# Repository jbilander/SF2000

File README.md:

# SF2000
Spitfire 2000, A low-end 42 MHz Amiga Accelerator based on the Motorola 68SEC000 CPU
 
***
 
This is WORK IN PROGRESS, a DIY hobby project. If you are going to make and sell boards you are also the one doing the customer support.
 
**Revision 3A is brand new and has not been tested yet.**
 
IMPORTANT **Please do not build Revision 2B.** We have found problems with the bus isolation on that revision which cause SRAM corruption. The Rev. 2B and Rev. 1B bills of material further down are kept for reference only.
 
***
 
The firmware for this board is in a separate repository available here: <br />
https://github.com/jbilander/SF2000-FW
<br />
 
***
 
Revision 3A
<br />

<br />
Full schematic: <a href="images/SF2000_rev3a_schematic.pdf">SF2000_rev3a_schematic.pdf</a>
 
***
 
Revision 1B
<br />

***

***
 
BOM Rev. 3A
---------
Rev. 3A replaces the four asynchronous SRAMs with a single SDRAM, swaps the Efinix Trion for an Intel/Altera MAX 10,
drops the on-board IDE interface, and adds an ESP32-C5 module and an RP2354A. Values and packages below are taken
straight from the KiCad netlist.
 
Designator  | Name/Value   | Package | Notes
-|-|-|-|
U1 | Voltage Regulator 3.3V, <br /> LM1117-3.3 or <br /> AMS1117-3.3 | SOT-223 | 3.3V 1A Low Drop-Out (LDO) Linear Voltage Regulator, main `3V3` rail <br />[LM111733QDCYRQ1](https://www.mouser.com/en/ProductDetail/595-LM111733QDCYRQ1) is the automotive-qualified LM1117-3.3 in SOT-223-4; any ordinary LM1117-3.3 in SOT-223 does the same job, and AMS1117-3.3 from AliExpress is a cheap alternative
U2 | Voltage Regulator 4.3V, ABLIC S-1132B43-M5T1U or TPS73643DBVR | SOT-23-5 | 4.3V LDO, the `4V3` supply rail for the CBT FET bus switches U4,U5,U6 <br />[S-1132B43-M5T1U](https://www.mouser.com/en/ProductDetail/628-S-1132B43-M5T1G)
U3 | Voltage Regulator 3.3V, TLV75533PDBVR | SOT-23-5 | 3.3V 500mA LDO, separate `3V3_C5` rail for the ESP32-C5 module so its Wi-Fi bursts stay off the FPGA rail <br />[TLV75533PDBVR](https://www.mouser.com/en/ProductDetail/595-TLV75533PDBVR)
U4,U5 | Digital Bus Switch 24-Bit FET, SN74CBT16211CDGGR or SN74CBT16811CDGGR | TSSOP-56 | FET level-shifter, Amiga +5V bus <-> 3V3 <br />[SN74CBT16211CDGGR](https://www.mouser.com/en/ProductDetail/595-SN74CBT16211CDGG) (Mouser's own part number drops the trailing R, but it is the cut-tape CDGGR)
U6 | Digital Bus Switch 10-Bit FET, SN74CBT3244PW | TSSOP-20 | FET level-shifter for the remaining control lines <br />[SN74CBT3244PW](https://www.mouser.com/en/ProductDetail/595-SN74CBT3244PW)
U7 | Bus Transceiver 16-Bit, SN74LVC16245ADGGR | TSSOP-48 | Buffers the D0-D15 data bus, direction and output-enable driven by the FPGA (`DATA_DIR`, `OE_D_HIGH`, `OE_D_LOW`) <br />[SN74LVC16245ADGGR](https://www.mouser.com/en/ProductDetail/595-SNLVC16245ADGGR)
U8 | Intel/Altera MAX 10 FPGA, 10M04SCU324C8G | BGA-324, 15x15mm, 0.8mm pitch | 4000 LE, internal configuration flash and UFM. It has to be the `S` **single-supply** variant - there is no 1.2V core rail on this board. The symbol and footprint in KiCad are drawn as a 10M02 so the design can be downsized to a 10M02SCU324 later if it fits; the firmware is developed for the 10M04 <br />[10M04SCU324C8G](https://www.mouser.com/en/ProductDetail/989-10M04SCU324C8G) / [10M02SCU324C8G](https://www.mouser.com/en/ProductDetail/989-10M02SCU324C8G)
U9 | W25Q16JVSNIQ 16 Mbit SPI NOR Flash memory | SOIC-8_3.9x4.9mm_P1.27mm (150-mil Narrow JEDEC SOIC) | [W25Q16JVSNIQ](https://www.digikey.com/en/products/detail/winbond-electronics/w25q16jvsniq/6193768) or [AT25SF161B-SSHD-T](https://www.mouser.com/en/ProductDetail/724-AT25SF161BSSHDT)
U10 | Motorola CPU MC68SEC000AA20 20MHz | QFP-64_14x14mm_Pitch0.8mm | [MC68SEC000AA20](https://shop.tvsat.com.pl/en_GB/searchquery/68sec000/1/phot/5?url=68sec000)
U11 | SDRAM 8Mx16 (128 Mbit), <br /> IM1216SDBABG-6I or <br /> AS4C8M16SA-6BINTR | TFBGA-54, 8x8mm, 0.8mm pitch | Replaces the four SRAMs of Rev. 2B. 128 Mbit is 16 MB, which is the whole address space the MC68SEC000 can reach, so there is nothing to gain from a bigger part. The footprint is routed for all 13 address lines, so a 256 Mbit 16Mx16 part (AS4C16M16SA-6BIN) drops straight in as well should a large shadow RAM ever want one - unlikely, but the option costs nothing. On the 128 Mbit parts ball F9 (`A12`) is a no-connect, so the controller's row-address width has to match whichever density is fitted. On the Alliance part the `-6BINTR` suffix is cut tape and `-6BIN` is the tray version of the same device, which costs noticeably more <br />[IM1216SDBABG-6I](https://www.mouser.com/en/ProductDetail/822-IM1216SDBABG-6I) / [AS4C8M16SA-6BINTR](https://www.mouser.com/en/ProductDetail/913-4C8M16SA-6BINTR)
U12 | 74HCT2G14GV,125 Dual Schmitt Trigger Inverter | TSOP-6 / SOT457 / SC-74 | Drives the SD_LED header J9 and the /SD_ACTIVE pin J10 at +5V <br />[74HCT2G14GV,125](https://www.mouser.com/en/ProductDetail/771-HCT2G14GV125)
U13 | ESP32-C5-WROOM-1U-N8R8 | Module, 18 x 25.5mm, U.FL antenna connector | The `-1U` variant uses an external antenna, so no PCB antenna keep-out is needed under or beside the module. If you fit the PCB-antenna `-1` variant instead, the module has to be moved so its antenna end hangs over the board edge <br />[ESP32-C5-WROOM-1U-N8R8](https://www.mouser.com/en/ProductDetail/356-ESP32C5WRM1UN8R8) / [ESP32-C5-WROOM-1-N8R8](https://www.mouser.com/en/ProductDetail/356-ESP32C5WROM1N8R8)
U14 | Level shifter 74LVC8T245PW,118 | TSSOP-24 | Clockport data bus CP_D0-CP_D7. 3V3 on the A side, +5V on the B side, direction and enable from the FPGA <br />[74LVC8T245PW,118](https://www.mouser.com/en/ProductDetail/771-74LVC8T245PW118)
U15 | Level shifter 74LVC8T245PW,118 | TSSOP-24 | Clockport address and control (CP_A2-CP_A5, /CS, /IORD, /IOWR). +5V on the A side, 3V3 on the B side, DIR and /OE tied low so it always drives 3V3 -> +5V <br />[74LVC8T245PW,118](https://www.mouser.com/en/ProductDetail/771-74LVC8T245PW118)
U16 | Raspberry Pi RP2354A | QFN-60, 7x7mm, 0.4mm pitch | MCU with 2 MB stacked flash. SPI slave to the FPGA (`SS_RP2354`, `IRQ_RP2354`) plus a UART link to the ESP32-C5 <br />[RP2354A (SC1511-A4)](https://www.mouser.com/en/ProductDetail/358-SC151113)
U17 | 74LVC1G57GV Configurable Multiple-Function Gate | TSOP-6 / SOT457 / SC-88A | Wired as XNOR with A and B tied together: CLK7M = CCK XNOR CCKQ (replaces the SN74LVC2G86DCUR XOR of Rev. 2B). This is how the 7 MHz is generated on every supported machine - the real 7M is not present on the co-pro slot of the early German A2000, nor on A500 Rev 3 and Rev 5, but CCK and CCKQ always are <br />[74LVC1G57GV,125](https://www.mouser.com/en/ProductDetail/771-LVC1G57GV125)
J1 | Goldfingers on PCB, 86-pin | ENIG | Order PCB with Goldfingers, ENIG and 45 degrees chamfered edge (or chamfer the edge yourself with a file)
J2 | CFGIN-header, Two-Pin Header | 2.54mm (1 x 2) | Put a jumper shunt here to activate autoconfig, or a CONFIGOUT-wire from another device into pin 2. Pin 2 is pulled up to +5V by R21
J3 | JTAG-header | Dual row 2.54mm (2 x 5) Pin Male Header |
J4 | JP-header JP2, JP3 | 2.54mm (2 x 2) Pin Male Header | JP2 = Generate E-CLK (if the internal 68k is removed from the socket), JP3 = MapROM
J5 | SWD pads, SWCLK / GND / SWDIO | 2.54mm (1 x 3) | Serial Wire Debug for U16 (RP2354A)
J6 | ESP32 UART0, TX0 / RX0 | 2.54mm (1 x 2) Pin Male Header | Console and flashing header for U13
J7 | VCC/GND Two-Pin Header | 2.54mm (2 x 1) | VIN +5V <br /> used when programming the FPGA standalone (card not installed in the Amiga). Be careful with orientation, check polarity BEFORE plugging-in a phone charger or similar here
J8 | GCT MEM2055-00-190-01-A Micro SD Card Socket | 9-pin push-pull micro-SD socket | Wired for 4-bit SDIO as well as 1-bit SPI: SD_CS=DAT3, SD_MOSI=CMD, SD_MISO=DAT0, SD_D1=DAT1, SD_D2=DAT2
J9 | SD_LED header, Two-Pin Header | 2.54mm (2 x 1) | Driven by U12 inverter buffer when /SD_CS is being asserted. Connect here to drive an external HDD-LED
J10 | SD_ACTIVE low signal, Right angle Single-Pin Header | 0.64 mm square pin angled | Driven by U12 inverter buffer when /SD_CS is being asserted. Connect from here to a [LED-board](https://github.com/jbilander/A500_IDE_LED_board) (Active low +5V-signal)
J11 | RP2354A UART0, TX0 / RX0 | 2.54mm (1 x 2) Pin Male Header | Console header for U16
J12 | CLOCKPORT-header | 2.00mm 22-Pin (2x11) Pin Male Header | Caution: This header is +5V levels. Be careful with orientation
J13 | JP-header JP1 | 2.54mm (2 x 1) Pin Male Header | 7 MHz / Turbo selector
J14 | USB-C Receptacle USB 2.0, HRO TYPE-C-31-M-12 | 16-pin SMD | Native USB for the ESP32-C5 (U13)
J15 | SPI-header: CS0, PROG_DET, SCK, MISO, MOSI, GND | 2.54mm (1 x 6) Pin Male Header | External SPI access to U9. `PROG_DET` tells the FPGA that a programmer is attached so it releases the bus
J16 | USB-C Receptacle USB 2.0, HRO TYPE-C-31-M-12 | 16-pin SMD | Native USB for the RP2354A (U16), UF2 / BOOTSEL
S1 | 4-way DIP switch, TDB04H0SB1R | SMD, 1.27mm pitch | Autoconfig fast-RAM size, RAMSZ0-RAMSZ3. Pulled up by RN1, so **all switches OFF, or the switch not fitted at all, means 8 MB**
X1 | Crystal Oscillator 20 MHz | Oscillator 5.0 x 3.2mm, 4-pad | **Do not populate.** Every internal clock is derived from the 7 MHz reconstructed by U17, through the FPGA PLL. X1 is kept in the design in case a free-running clock is needed later; it lands on a dedicated clock input (CLK0p) through R3. Leave the pads empty until then
Y1 | Crystal 12 MHz, ABM8-272-T3 | 3.2 x 2.5mm, 4-pad | CL = 10 pF, +/-30 ppm. With C49/C50 = 15 pF and R12 = 1k this is the RP2350/RP2354 reference oscillator circuit <br />[ABM8-272-T3](https://www.digikey.com/en/products/detail/abracon-llc/ABM8-272-T3/22472366)
L1 | Inductor 3.3uH, AOTA AB201610S3R3101T | 2.0 x 1.6mm SMD shielded power inductor | Switching inductor for the RP2354A internal core buck regulator (`VREG_LX`)
BT1,BT2 | Tactile push button | 3 x 4 x 2mm SMD, 2-pin | BT1 = BOOT (pulls `BOOTSEL` low through R13), BT2 = RESET (pulls `RUN` low) for U16
BT3,BT4 | Tactile push button | 3 x 4 x 2mm SMD, 2-pin | BT3 = BOOT (IO28 strap), BT4 = EN/RESET for U13
R1 | 22 Ω Resistor | 0603 | Series damping on `CLK_SDRAM`, straight off the FPGA PLL output pin
R2 | 33 Ω Resistor | 0603 | Series damping on the 7 MHz generated by U17, into the FPGA clock input
R3 | 33 Ω Resistor | 0603 | Series damping on `OSC_CLK` from X1 (only relevant if X1 is fitted)
R4 | 33 Ω Resistor | 0603 | Series damping on `CLKCPU` from the FPGA to U10
R5 | 33 Ω Resistor | 0603 | Series damping on SPI MOSI
R6 | 33 Ω Resistor | 0603 | Series damping on SPI SCLK
R7 | 33 Ω Resistor | 0603 | Series damping on `SD_CLK` to the micro SD card
R8 | 33 Ω Resistor | 0603 | RC filter into the RP2354A `VREG_AVDD` analog supply, together with C9
R9,R10 | 27 Ω Resistor | 0603 | USB series resistors for D+ / D- on J16
R11 | 330 Ω Resistor | 0603 | Series resistor for the SD_LED header J9, adjust to your LED and preferred brightness
R12 | 1k Ω Resistor | 0603 | Series resistor on `XOUT` of Y1 (RP2354A reference circuit)
R13 | 1k Ω Resistor | 0603 | Series resistor between `BOOTSEL` and the BOOT button BT1
R14 | 4.7k Ω Resistor | 0603 | Pull-up for `RUN` on U16, with C44 as the reset delay
R15,R16 | 5.1k Ω Resistor | 0603 | USB-C CC1 / CC2 pull-downs for J16
R17,R18 | 5.1k Ω Resistor | 0603 | USB-C CC1 / CC2 pull-downs for J14
R19 | 10k Ω Resistor | 0603 | Pull-up for JTAG `TDI` to 3V3
R20 | 10k Ω Resistor | 0603 | Pull-down for JTAG `TCK`
R21 | 10k Ω Resistor | 0603 | Pull-up for /CFGIN to +5V (J2 pin 2)
R22 | 10k Ω Resistor | 0603 | Pull-up for `ESP32_RTS`
R23 | 10k Ω Resistor | 0603 | Pull-down for `PROG_DET`
R24 | 10k Ω Resistor | 0603 | Pull-up for the ESP32-C5 `EN` pin, forms an RC reset delay with C46
R25 | 10k Ω Resistor | 0603 | Pull-up for `CP_D_OE` on the 3V3 side
R26,R27 | 10k Ω Resistor | 0603 | Pull-ups for JP2 and JP3
RN1 | Resistor pack 10k Ω (CAY16-103J4LF) | 1206 | Pull-ups for RAMSZ0-RAMSZ3 (S1) <br />[CAY16-103J4LF](https://www.digikey.com/en/products/detail/bourns-inc/cay16-103j4lf/431579)
RN2 | Resistor pack 10k Ω (CAY16-103J4LF) | 1206 | Pull-ups for JP1, `TMS`, `CONF_DONE` and `nSTATUS`
RN3 | Resistor pack 10k Ω (CAY16-103J4LF) | 1206 | Pull-ups for `ESP32_CTS`, `nCONFIG`, `SD_D2` and `SD_CS`
RN4 | Resistor pack 10k Ω (CAY16-103J4LF) | 1206 | Pull-ups for `SD_CD`, `SD_D1`, `SD_MISO` and `SD_MOSI`
RN5 | Resistor pack 10k Ω (CAY16-103J4LF) | 1206 | Pull-ups for `CP_IOWR`, `CP_IORD`, `CP_CS` (3V3 side) and `SS_W25Q16`
RN6 | Resistor pack 10k Ω (CAY16-103J4LF) | 1206 | Pull-ups to **+5V** for `RST`, `CP_RTC_CS`, `CP_RTC_DS` and `CP_INT6` on the clockport
C1 | Polarized Electrolytic Capacitor 100uF | CP_Elec_6.3x7.7 mm | [Wurth SMD WCAP-AS5H 100uF](https://www.digikey.com/en/products/detail/w%C3%BCrth-elektronik/865230245004/5727885)
C2 | Polarized Electrolytic Capacitor 22uF | CP_Elec_5x5.8 mm | [Wurth SMD WCAP-AS5H 22uF](https://www.digikey.com/en/products/detail/w%C3%BCrth-elektronik/865230342002/5727846)
C3-C8 | Ceramic Capacitor 10uF | 1206 | Bulk on the 3V3, 4V3, 3V3_C5 and clockport +5V rails
C9-C11 | Ceramic Capacitor 4.7uF | 1206 | RP2354A supplies and core buck output
C12 | Ceramic Capacitor 0.47uF = 470nF | 1206 |
C13 | Ceramic Capacitor 0.22uF = 220nF | 1206 | Local reservoir at the ESP32-C5 3V3 pin
C14-C19 | Ceramic Capacitor 0.1uF = 100nF | 0805 |
C20-C46 | Ceramic Capacitor 0.1uF = 100nF | 0603 | Decoupling
C47,C48 | Ceramic Capacitor 0.01uF = 10nF | 0603 |
C49,C50 | Ceramic Capacitor 15pF | 0603 | Load capacitors for Y1
C51-C72 | Ceramic Capacitor 0.1uF = 100nF | 0402 | The cluster on the underside directly beneath U8 and U11
 
***
 
### Rev. 3A board layout
 
Four layer stackup. The top and bottom layers carry the signal routing with a GND pour filling the gaps,
the second layer is a solid GND plane and the third layer is a 3.3V plane.
<br />
Top layer, and the GND plane on inner layer 1:
<br />

<br />
The 3.3V plane on inner layer 2, and the bottom layer:
<br />

***
 
BOM Rev. 2B
---------
Designator  | Name/Value   | Package | Notes
-|-|-|-|
U1 | Voltage Regulator 3.3V, <br /> LM1117-3.3 or <br /> AMS1117-3.3 | SOT-223 | 3.3V 1A Low Drop-Out (LDO) Linear Voltage regulator
U2 | Voltage Regulator 4.3V, ABLIC S-1132B43-M5T1U or TPS73643DBVR | SOT-23-5 | 4.3V LDO Linear Voltage Regulator<br />[S-1132B43-M5T1U](https://www.digikey.com/en/products/detail/ablic-inc/S-1132B43-M5T1U/6112740)
U3 | Voltage Regulator 1.2V, TLV73312PDBVR | SOT-23-5 | 1.2V LDO Linear Voltage Regulator<br />[TLV73312PDBVR](https://www.digikey.com/en/products/detail/texas-instruments/TLV73312PDBVR/5022371)
U4,U5,U6 | Digital Bus Switch ICs 24-Bit FET, SN74CBT16211CDGGR or SN74CBT16811CDGGR | TSSOP-56 | FET Level-shifter <br />[SN74CBT16211CDGGR](https://www.digikey.com/en/products/detail/texas-instruments/SN74CBT16211CDGGR/864169) or <br />[SN74CBT16811CDGGR](https://www.digikey.com/en/products/detail/texas-instruments/sn74cbt16811cdggr/864186)
U7 | Dual XOR gate SN74LVC2G86DCUR | VSSOP-8_2.3x2mm_P0.5mm | Generates 7 MHz CLK from ~(CCK XOR CCKQ) <br />[SN74LVC2G86DCUR](https://www.digikey.com/en/products/detail/texas-instruments/sn74lvc2g86dcur/484697)
U8 | Efinix Trion T8 FPGA T8Q144C3 | LQFP-144_20x20mm_P0.5mm | FPGA - Field Programmable Gate Array, 7384 LE, 97 I/O <br />[T8Q144C3](https://www.digikey.com/en/products/detail/efinix-inc/t8q144c3/11591370)
U9 | W25Q16JVSNIQ 16 Mbit SPI NOR Flash memory | SOIC-8_3.9x4.9mm_P1.27mm (150-mil Narrow JEDEC SOIC) | [W25Q16JVSNIQ](https://www.digikey.com/en/products/detail/winbond-electronics/w25q16jvsniq/6193768) or [AT25SF161B-SSHD-T](https://www.digikey.com/en/products/detail/renesas-electronics-corporation/AT25SF161B-SSHD-T/14549318)
U10 | Motorola CPU MC68SEC000AA20 20MHz | QFP-64_14x14mm_Pitch0.8mm | [MC68SEC000AA20](https://shop.tvsat.com.pl/en_GB/searchquery/68sec000/1/phot/5?url=68sec000)
U11 | SST39LF802C-55-4C-EKE or SST39LF800A-55-4C-EKE | TSOP-I-48_18.4x12mm_P0.5mm | NOR Flash 3.0 to 3.6V 8Mbit Multi-Purpose Flash (for Kickstart) <br />[S39LF802C554CEKE](https://www.mouser.com/ProductDetail/579-S39LF802C554CEKE)<br />[S39LF800A554CEKE](https://www.digikey.com/en/products/detail/microchip-technology/SST39LF800A-55-4C-EKE/2297824)
U12 | 74AHCT14PW, Six Channel Schmitt Trigger Inverter | TSSOP-14_4.4x5mm_P0.65mm | [74AHCT14PW,118](https://www.digikey.com/en/products/detail/nexperia-usa-inc/74AHCT14PW-118/1229627) or <br />[SN74AHCT14PWR](https://www.digikey.com/en/products/detail/texas-instruments/SN74AHCT14PWR/276754)
U13 | NOR Flash SST39LF040-55-4C-NHE-T | PLCC-32 | NOR Flash 3.0 to 3.6V <br />[SST39LF040554CN](https://www.digikey.com/en/products/detail/microchip-technology/sst39lf040-55-4c-nhe-t/4080132) <br /> (or 39LF020, 39LF010)
U14,U15 | SRAM ISSI IS61WV20488FBLL-10TLI  | TSOP-44 | First 4 MB SRAM <br />High-Speed, Async, 2Mbx8, 10ns, 2.4v-3.6v, 44 Pin TSOP II, RoHS <br />[IS61WV20488FBLL-10TLI](https://www.mouser.com/ProductDetail/870-61W20488FBLL10TI)
U16,U17 | SRAM ISSI IS61WV20488FBLL-10TLI  | TSOP-44 | Second 4 MB (Optional) --"-- <br />
J1 | Goldfingers on PCB | ENIG | Order PCB with Goldfingers, ENIG and 45 degrees chamfered edge (or chamfer the edge yourself with a file)
J2 | CFGIN-header Two-Pin Header | 2.54mm pitch | Put a Jumper shunt here to activate autoconfig, or a CONFIGOUT-wire from other device to the right (pin 2) in this header.  
J3 | JTAG-header   | Dual row 2.54mm (2 x 5) Pin Male Header | 
J4 | JP-header JP2 | 2.00mm (2 x 1) Pin Male Header | Generate E-CLK (if internal 68k is removed from socket)
J5 | JP-header JP3 | 2.00mm (2 x 1) Pin Male Header | Rom overlay jumper
J6 | JP-header JP4 | 2.00mm (2 x 1) Pin Male Header | 4/8 MB SRAM Config
J7 | VCC/GND Two-Pin Header | 2.54mm pitch | VIN +5V <br /> used when programming FPGA standalone (card not installed in the Amiga). Be careful with orientation, check polarity BEFORE plugging-in a phone charger or similar here.
J8 | Sunrom Micro SD Card Holder | 9-pin Micro SD card slot connector | [Sunrom Micro-SD card holder](https://www.aliexpress.com/item/32802051702.html)
J9 | SD_LED header, Two-Pin Header | 2.54mm pitch | Driven by U12 inverter buffer when /SD_CS is being asserted. Connect to here in order to drive an external HDD-LED
J10 | SD_ACTIVE low signal, Right angle Single-Pin Header | 0.64 mm square pin angled | Driven by U12 inverter buffer when /SD_CS is being asserted. Connect to here in order to drive a [LED-board](https://github.com/jbilander/A500_IDE_LED_board) (Active low +5V-signal)
J11 | Rom-bank selector | 2.00mm (2 x 1) Pin Male Header | Select first or second bank, address line A15 (pin 3) on U13 (SST39LF040)
J12 | CLOCKPORT-header | 2.00mm 22-Pin (2x11) Pin Male Header | Caution: This header is +5V levels. Be careful with orientation.
J13 | JP-header JP1 | 2.54mm (2 x 1) Pin Male Header | 7 MHz / Turbo selector
X1 | Crystal Oscillator 20 MHz | Oscillator_7.0x5.0mm |
R1 | 33 Ω Resistor | 0805 | Damping resistor for 20 MHz clock-signal coming from X1 oscillator
R2 | 33 Ω Resistor | 0805 | Damping resistor for 7 MHz clock-signal coming from U7 (SN74LVC2G86DCUR)
R3 | 33 Ω Resistor | 0805 | Damping resistor for CLKCPU clock-signal coming from FPGA pin 33
R4 | ~220 Ω Resistor | 0805 | Series resistor for SD_LED header J9, adjust R-value to your type of LED and preferred brightness
R5 | 10k Ω Resistor | 0805 | Pull-up resistor for /FLASH_OE to 3V3
R6 | 10k Ω Resistor | 0805 | Pull-up resistor for JP2 to 3V3
R7 | 10k Ω Resistor | 0805 | Pull-up resistor for /CFGIN to 5V
R8 | 100k Ω Resistor | 0805 | Pull-up resistor for CRESET_N to 3V3
RN1-RN6 | Resistor pack 10k Ω (CAY16-103J4LF) | 1206 | [CAY16-103J4LF](https://www.digikey.com/en/products/detail/bourns-inc/cay16-103j4lf/431579)
C1 | Polarized Electrolytic Capacitor 100uF | CP_Elec_6.3x7.7 mm | [Wurth SMD WCAP-AS5H 100uF](https://www.digikey.com/en/products/detail/w%C3%BCrth-elektronik/865230245004/5727885)
C2 | Polarized Electrolytic Capacitor 22uF | CP_Elec_5x5.8 mm | [Wurth SMD WCAP-AS5H 22uF](https://www.digikey.com/en/products/detail/w%C3%BCrth-elektronik/865230342002/5727846)
C3-C7 | Ceramic Capacitor 10uF | 1206 |
C8 | Ceramic Capacitor 2.2uF | 1206 |
C9 | Ceramic Capacitor 0.47uF = 470 nF | 1206 |
C10-C39 | Ceramic Capacitor 0.1uF = 100nF | 0805 | 
C40-C54 | Capacitor 0.01uF = 10nF | 0805 |
 
***
 
BOM Rev. 1B
---------
Designator  | Name/Value   | Package | Notes
-|-|-|-|
U1 | Voltage Regulator 3.3V, <br /> LM1117-3.3 or <br /> AMS1117-3.3 | SOT-223 | 3.3V 1A Low Drop-Out (LDO) Voltage regulator. https://www.aliexpress.com/item/32869037691.html
U2 | Voltage Regulator 4.3V, TPS73643DBVR or <br /> ABLIC S-1200B43-M5T1U or <br /> MIC5205YM5-TR ADJ (with R1,R2 and C7 populated) | SOT-23-5 | 4.3V LDO Voltage Regulator<br />* [TPS73643DBVR](https://www.mouser.com/ProductDetail/595-TPS73643DBVR) <br />* [S-1132B43-M5T1U](https://www.mouser.com/ProductDetail/628-S-1132B43-M5T1G) <br />* [MIC5205YM5-TR](https://www.mouser.com/ProductDetail/Microchip-Technology-Atmel/MIC5205YM5-TR?qs=U6T8BxXiZAUCsfGqlmZYIw%3D%3D) (Adjustable, populate R1,R2,C7)
U3 | Inverter Schmitt Trigger 74LVC2G14GV,125 | TSOP-6/SOT457/SC-74 | * [LVC2G14GV125](https://www.mouser.com/ProductDetail/771-LVC2G14GV125)
U4,U5,U6 | Digital Bus Switch ICs 24-Bit FET, SN74CBT16211ADGGR | TSSOP-56 | FET Level-shifter <br /> * [SN74CBT16211ADGGR](https://www.mouser.com/ProductDetail/595-SNCBT16211ADGGR) <br /> * [SN74CBT16811CDGG](https://www.mouser.com/ProductDetail/595-SN74CBT16811CDGG)
U7 | XNOR gate w/ Schmitt Trigger SN74AUP1T87DCKR |TSSOP-5/SC-70-5/SOT-353-1 | Generates 7 MHz CLK from CCK XNOR CCKQ <br /> * [SN74AUP1T87DCKR](https://www.mouser.com/ProductDetail/595-SN74AUP1T87DCKR)
U8 | Gowin FPGA GW1N-UV9LQ144C6/I5 | LQFP-144 | FPGA - Field Programmable Gate Array, 8640 LE, 120 I/O <br /> * [GW1N-UV9LQ144C6/I5](https://www.mouser.com/ProductDetail/192-GW1NUV9LQ144C6I5)
U9 | Motorola CPU MC68SEC000AA20 | QFP-64 | MPU 32-bit 20MHz <br /> Contact Eriond to buy a NOS CPU for a reasonable price
U10,U11 | SRAM ISSI IS61WV20488FBLL-10TLI  | TSOP-44 | First 4 MB SRAM <br />High-Speed, Async, 2Mbx8, 10ns, 2.4v-3.6v, 44 Pin TSOP II, RoHS <br /> * [61W20488FBLL10TI](https://eu.mouser.com/ProductDetail/870-61W20488FBLL10TI)
U12,U13 | SRAM ISSI IS61WV20488FBLL-10TLI  | TSOP-44 | Second 4 MB (Optional) --"-- <br />
U14 | NOR Flash SST39LF040-55-4C-NHE-T | PLCC-32 | NOR Flash 3.0 to 3.6V (For Oktagon/Oktapus. IDE-driver) <br /> * [SST39LF040554CN](https://www.mouser.com/ProductDetail/579-SST39LF040554CN) <br /> (or 39LF020, 39LF010)
U15 | SST39LF802C-55-4C-EKE | TSOP-48 | NOR Flash 3.0 to 3.6V 8Mbit Multi-Purpose Flash (for Kickstart) <br /> * [S39LF802C554CEKE](https://www.mouser.com/ProductDetail/579-S39LF802C554CEKE)
U16,U17,U18 | Bus Transceiver 74LVC245APW,118  | TSSOP-20 | * [74LVC245APW-T](https://www.mouser.com/ProductDetail/771-74LVC245APW-T)
J1 | Goldfingers on PCB | ENIG | Order PCB with Goldfingers, ENIG and 45 degrees chamfered edge (or chamfer the edge yourself)
J2 | JTAG-header | Dual row 2.54mm (2 x 5) Pin Male Header Strip | 
J3 | JP-header JP2,JP3,JP4 | Dual row 2.00mm (2 x 3) Pin Male Header Strip | Turbo speed selector
J4 | JP-header JP5 | 2.00mm (2 x 1) Pin Male Header | Generate E-CLK (if internal 68k is removed from socket)
J5 | IDE/ATA-header | 2.00mm 44-Pin (2x22 Pin) Straight Male Shrouded PCB Box header IDC Socket | For A2000: <br /> * [Shrouded header](https://www.aliexpress.com/item/1720053014.html) <br />For A500 internal mount a right angled female header can be used (2x25 and cut down to 2x22): <br /> * [Right Angle Female Connector](https://www.aliexpress.com/item/4001286548060.html)
J6 | Sunrom Micro SD Card Holder | 9-pin Micro SD card slot connector | * [Sunrom Micro-SD card holder](https://www.aliexpress.com/item/32802051702.html)
J7 | VCC/GND Two-Pin Header 2.54mm pitch | 2.54mm pitch | VIN +5V <br /> used when programming FPGA standalone (card not installed in the Amiga). Be careful with orientation, check polarity BEFORE plugging-in a phone charger or similar here.
J8 | JP-header JP6 | 2.00mm (2 x 1) Pin Male Header | 4/8 MB SRAM Config
J9,J10 | JP-header JP7,JP8 | 2.00mm (2 x 2) Pin Male Header | JP7 Autoboot IDE OFF/ON Selector, JP8 Oktagon/Oktapus. IDE-driver Selector
J11 | LED Two-Pin Header 2.54mm pitch | 2.54mm pitch | Driven by U3 inverter buffer when /Active on IDE is being asserted. Connect to here to drive an external HDD-LED
J12 | /Active signal, Single-Pin Header 2.54mm | 2.54mm pitch | /Active signal from IDE. Connect from here to a <br /> * [LED-board](https://github.com/jbilander/A500_IDE_LED_board) 
J13 | Pmod Type 2A (SPI) Female header, 12-Pin (2x6) | 2.54mm pitch |  For connecting SPI peripherals. <br /> * [Right-Angled](https://www.aliexpress.com/item/1005003223096006.html) (A2000) or <br /> * [Straight](https://www.aliexpress.com/item/1005003335405213.html) (A500) to not interfere with [RGBtoHDMI-adapter](https://github.com/jbilander/A500_RGBtoHDMI) inside A500
R1 | 1.2k Ω Resistor | 0805 | Feedback resistor, Only populate if U2 is of ADJ-ustable type (e.g. MIC5205YM5-TR)
R2 | 3k Ω Resistor | 0805 | Feedback resistor, Only populate if U2 is of ADJ-ustable type (e.g. MIC5205YM5-TR)
R3 | 10k Ω Resistor | 0805 | Pull-up resistor for /CFGIN (5V-side)
R4 | 10k Ω Resistor | 0805 | Pull-up resistor in RC-debounce circuit
R5 | 10k Ω Resistor | 0805 | Series resistor in RC-debounce circuit
R6 | ~220 Ω Resistor | 0805, 200 mW | Series resistor for IDE-LED header J11, adjust R-value to your type of LED and preferred brightness
R7 | 1k Ω Resistor | 0805 | Pull-down resistor for IDE_IRQ
R8 | 4.7k Ω Resistor | 0805 | Pull-up resistor for IDE_IORDY
R9 | 10k Ω Resistor | 0805 | Pull-up resistor for JP6
R10 | 1k Ω Resistor | 0805 | Pull-down resistor for MODE0 (Gowin FPGA boot/configure from embFlash)
R11 | 1k Ω Resistor | 0805 | Pull-down resistor for MODE1 (Gowin FPGA boot/configure from embFlash)
R12 | 10k Ω Resistor | 0805 | Pull-up resistor for RECONFIG_N (Gowin FPGA) and /SPI_CS (in J13 Pmod-header)
R13 | 10k Ω Resistor | 0805 | Pull-up resistor for /ACTIVE (IDE)
RN1-RN2,RN5 | Resistor pack 10k Ω (CAY16-103J4LF) | 1206 | * [CAY16-103J4LF](https://www.mouser.com/ProductDetail/652-CAY16-103J4LF) Pull-up resistors.
RN3-RN4 | Resistor pack 10k Ω (CAY16-103J4LF) or 4.7k (CAY16-4701F4LF) | 1206 | * [CAY16-4701F4LF](https://www.mouser.com/ProductDetail/652-CAY16A-4701F4LF) Pull-up resistors for SD0-SD3,SD_CD,SD_CMD,JP7,JP8
C1-C2 | Capacitor 10uF | 1206 |
C3 | Capacitor 0.1uF = 100nF | 0805 |
C4 | Polarized Capacitor 100uF | CP_Elec_6.3x7.7 | * [Wurth SMD WCAP-AS5H 100uF](https://www.mouser.com/ProductDetail/710-865230245004)
C5 | Polarized Capacitor 22uF | CP_Elec_5x5.8 | * [Wurth SMD WCAP-AS5H 22uF](https://www.mouser.com/ProductDetail/710-865230342002)
C6 | Capacitor 10uF to 0.22uF | 1206 | Check datasheet for U2 what is suitable here.
C7 | Capacitor 0.33uF = 330nF | 1206 | (Not needed if U2 is TPS73643DBVR, check your U2-datasheet)
C8 | Capacitor 10uF | 1206 |
C9-C25 | Capacitor 0.1uF = 100nF | 0805 | C24 capacitor in RC-debounce circuit
C26-C27 | Capacitor 10uF | 1206 |
C28-C46 | Capacitor 0.01uF = 10nF | 0805 |
 
***
 
A SF2000 shared shopping cart with most of the stuff in the list, no 3V3-regulator though and not all birdseed (passives):
https://www.mouser.com/ProjectManager/ProjectDetail.aspx?AccessID=fdb374e26b
 
***
 
The FPGA used in this Accelerator board, please note it has to be the Voltage `UV` version because of 3.3V is being used for all VCC/VCCIO on the Accelerator:
<br />

***
 
### Ordering details (JLCPCB):

<br />

***
### MC68SEC000 
 
The SF2000 is based on the MC68SEC000 CPU <br />
https://www.nxp.com/docs/en/product-brief/MC68SEC000.pdf <br />

<br />
You can contact Eriond, https://github.com/eriond (over at A314 or Retro Tinkering or SUGA (Swedish User Group Amiga) discord) to buy a NOS MC68SEC000 at a reasonable price.
 
***
 
### Installing in A500 or A2000:
 
Internal A500 installation with this adapter: <br />
https://github.com/jbilander/A500_Edge_Expansion_adapter
<br />

<br />

<br />

External A500 installation with this adapter: <br />
https://github.com/jbilander/POC86
<br />

<br />

<br />

### A2000 Co-pro slot:<br />

***
 
### Building
 
Follow the dots to get the correct orientation of the chips when soldering, don't rely on the silkscreen text.
<br />

<br />
You can solder the 3V3 LDO and the FPGA first and then check that you can communicate via JTAG programming a simple LED-blink example or similar. +5V you can take from a USB phone-charger or similar, check polarity before you plug it in.
<br />

<br />
Make sure you populate the 4V3 LDO like this if you are using `TPS73643DBVR` or `ABLIC S-1200B43-M5T1U`, populating R1,R2,C7 is only for a ADJ-regulator to achieve 4V3.
<br />

<br />

<br />
For A2000 and ribbon cable use you can solder a 44 pin IDE-header like this:
<br />

***
 
### Performance
 
Some MC68SEC000 can be overclocked to 42 MHz and running with only one wait state for the IDE/ATA interface we can reach really good performance:
<br />

<br />
Flashing a ROM (in this case 3.1.4) to the FlashROM chip U15 (using LIV2's excellent sfflash-tool) and closing JP9 even better performance can be achieved:
<br />
<br />
Demo video: <br />
https://drive.google.com/file/d/1dCBK24LUC5VLB2dshrW_5n82D2emHB5-/view?usp=sharing
<br />
<br />

<br />

<br />
<br />
But for running more stable a few wait states can be added to the IDE/ATA, <br /> 
https://github.com/jbilander/SF2000-FW/blob/main/rtl/ata.v#L56 <br />
resulting in a bit slower IDE:
<br />
<br />

<br />
<br />
JTAG-header description:
<br />

***
 
Happy Hackin' 
 
***
 
[![CC BY-SA 4.0][cc-by-sa-shield]][cc-by-sa]
 
This work is licensed under a
[Creative Commons Attribution-ShareAlike 4.0 International License][cc-by-sa].
 
[![CC BY-SA 4.0][cc-by-sa-image]][cc-by-sa]
 
[cc-by-sa]: http://creativecommons.org/licenses/by-sa/4.0/
[cc-by-sa-image]: https://licensebuttons.net/l/by-sa/4.0/88x31.png
[cc-by-sa-shield]: https://img.shields.io/badge/License-CC%20BY--SA%204.0-lightgrey.svg

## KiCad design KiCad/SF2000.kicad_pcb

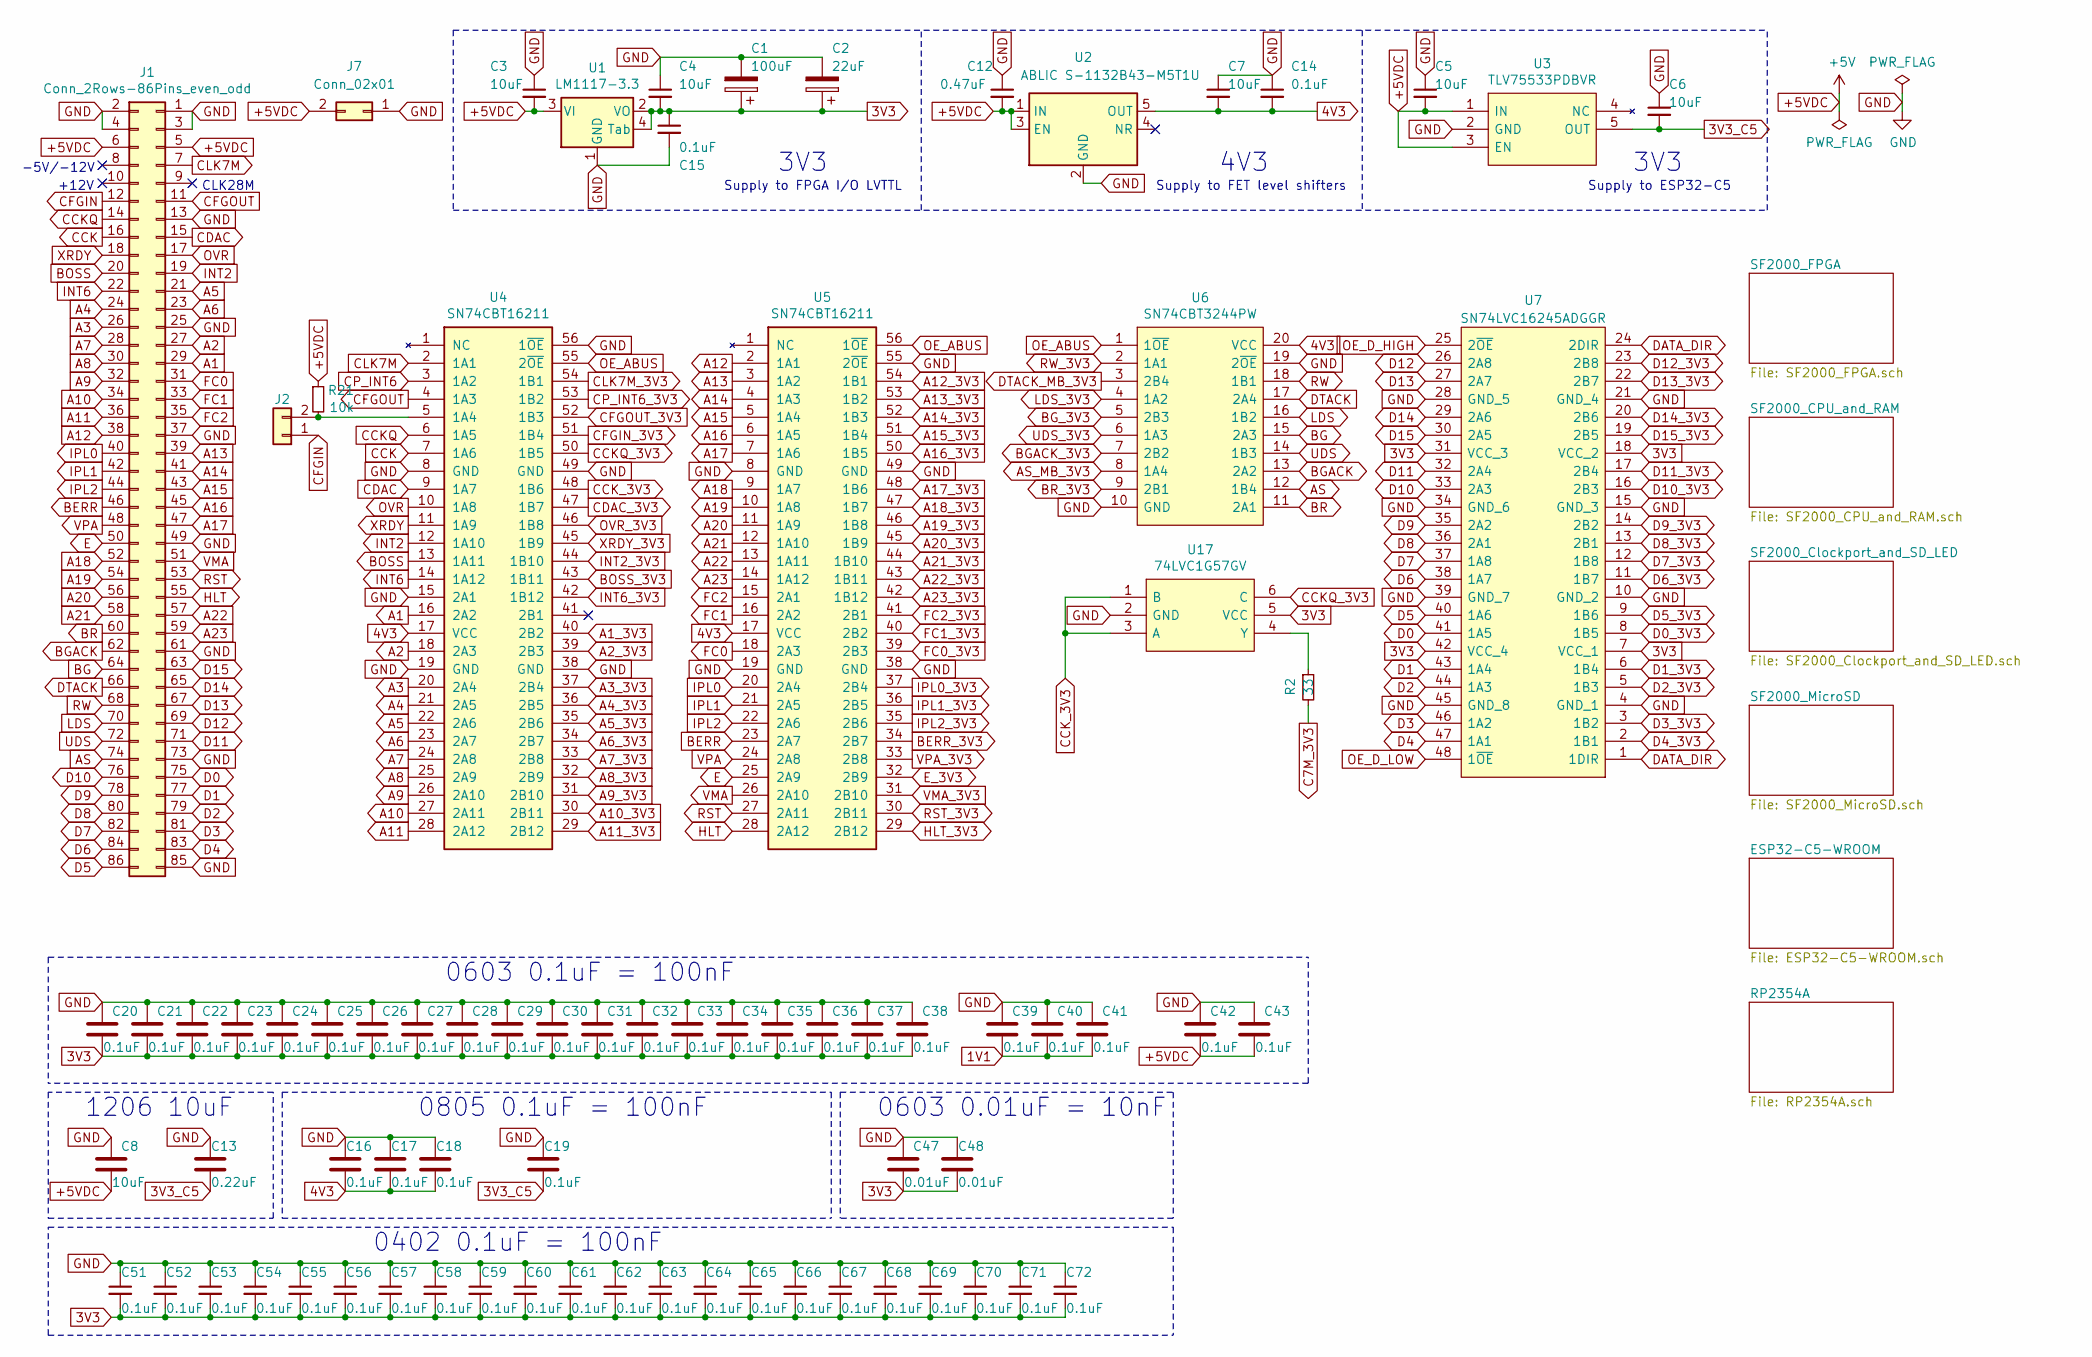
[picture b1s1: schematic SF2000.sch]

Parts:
C1: 100uF; CP_Elec_6.3x7.7
C2: 22uF; CP_Elec_5x5.8
C3, C4, C5, C7, C8: 10uF; C_1206_3216Metric_Pad1.42x1.75mm_HandSolder
C6: 10uF; C_1206_3216Metric_Pad1.33x1.80mm_HandSolder
C12: 0.47uF; C_1206_3216Metric_Pad1.42x1.75mm_HandSolder
C13: 0.22uF; C_1206_3216Metric_Pad1.33x1.80mm_HandSolder
C14, C15, C16, C17, C18: 0.1uF; C_0805_2012Metric_Pad1.15x1.40mm_HandSolder
C19: 0.1uF; C_0805_2012Metric_Pad1.18x1.45mm_HandSolder
C20, C21, C22, C23, C24, C25, C26, C27, C28, C29, C30, C31, C32, C33, C34, C35, C36, C37, C38, C39, C40, C41, C42, C43: 0.1uF; C_0603_1608Metric_Pad1.08x0.95mm_HandSolder
C47, C48: 0.01uF; C_0603_1608Metric_Pad1.08x0.95mm_HandSolder
C51, C52, C53, C54, C55, C56, C57, C58, C59, C60, C61, C62, C63, C64, C65, C66, C67, C68, C69, C70, C71, C72: 0.1uF; C_0402_1005Metric_Pad0.74x0.62mm_HandSolder
J1: Conn_2Rows-86Pins_even_odd; A500_86pin_Edge_Connector
J2: Conn_01x02; PinHeader_1x02_P2.54mm_Vertical
J7: Conn_02x01; PinHeader_2x01_P2.54mm_Vertical
R2: 33; R_0603_1608Metric_Pad0.98x0.95mm_HandSolder
R21: 10k; R_0603_1608Metric_Pad0.98x0.95mm_HandSolder
U1: LM1117-3.3; SOT-223
U2: ABLIC S-1132B43-M5T1U; SOT-23-5
U3: TLV75533PDBVR; SOT-23-5_HandSoldering
U4, U5: SN74CBT16211; TSSOP-56_6.1x14mm_P0.5mm
U6: SN74CBT3244PW; TSSOP-20_4.4x6.5mm_P0.65mm
U7: SN74LVC16245ADGGR; TSSOP-48_6.1x12.5mm_P0.5mm
U17: 74LVC1G57GV; TSOP-6_1.65x3.05mm_P0.95mm

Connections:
1V1: C39.2, C40.2, C41.2; also elsewhere on the board
3V3: C1.1, C2.1, C4.2, C15.1, C20.2, C21.2, C22.2, C23.2, C24.2, C25.2, C26.2, C27.2, C28.2, C29.2, C30.2, C31.2, C32.2, C33.2, C34.2, C35.2, C36.2, C37.2, C38.2, C47.2, C48.2, C51.2, C52.2, C53.2, C54.2, C55.2, C56.2, C57.2, C58.2, C59.2, C60.2, C61.2, C62.2, C63.2, C64.2, C65.2, C66.2, C67.2, C68.2, C69.2, C70.2, C71.2, C72.2, U1.2 (VO), U1.4 (Tab), U7.7 (VCC_1), U7.18 (VCC_2), U7.31 (VCC_3), U7.42 (VCC_4), U17.5 (VCC); also elsewhere on the board
3V3_C5: C6.2, C13.2, C19.2, U3.5 (OUT); also elsewhere on the board
4V3: C7.2, C14.2, C16.2, C17.2, C18.2, U2.5 (OUT), U4.17 (VCC), U5.17 (VCC), U6.20 (VCC)
+5VDC: C3.2, C5.2, C8.2, C12.2, C42.2, C43.2, J1.5, J1.6, J7.2, R21.1, U1.3 (VI), U2.1 (IN), U2.3 (EN), U3.1 (IN), U3.3 (EN); also elsewhere on the board
A1: J1.29, U4.16 (2A2)
A1_3V3: U4.40 (2B2); also elsewhere on the board
A2: J1.27, U4.18 (2A3)
A2_3V3: U4.39 (2B3); also elsewhere on the board
A3: J1.26, U4.20 (2A4)
A3_3V3: U4.37 (2B4); also elsewhere on the board
A4: J1.24, U4.21 (2A5)
A4_3V3: U4.36 (2B5); also elsewhere on the board
A5: J1.21, U4.22 (2A6)
A5_3V3: U4.35 (2B6); also elsewhere on the board
A6: J1.23, U4.23 (2A7)
A6_3V3: U4.34 (2B7); also elsewhere on the board
A7: J1.28, U4.24 (2A8)
A7_3V3: U4.33 (2B8); also elsewhere on the board
A8: J1.30, U4.25 (2A9)
A8_3V3: U4.32 (2B9); also elsewhere on the board
A9: J1.32, U4.26 (2A10)
A9_3V3: U4.31 (2B10); also elsewhere on the board
A10: J1.34, U4.27 (2A11)
A10_3V3: U4.30 (2B11); also elsewhere on the board
A11: J1.36, U4.28 (2A12)
A11_3V3: U4.29 (2B12); also elsewhere on the board
A12: J1.38, U5.2 (1A1)
A12_3V3: U5.54 (1B1); also elsewhere on the board
A13: J1.39, U5.3 (1A2)
A13_3V3: U5.53 (1B2); also elsewhere on the board
A14: J1.41, U5.4 (1A3)
A14_3V3: U5.52 (1B3); also elsewhere on the board
A15: J1.43, U5.5 (1A4)
A15_3V3: U5.51 (1B4); also elsewhere on the board
A16: J1.45, U5.6 (1A5)
A16_3V3: U5.50 (1B5); also elsewhere on the board
A17: J1.47, U5.7 (1A6)
A17_3V3: U5.48 (1B6); also elsewhere on the board
A18: J1.52, U5.9 (1A7)
A18_3V3: U5.47 (1B7); also elsewhere on the board
A19: J1.54, U5.10 (1A8)
A19_3V3: U5.46 (1B8); also elsewhere on the board
A20: J1.56, U5.11 (1A9)
A20_3V3: U5.45 (1B9); also elsewhere on the board
A21: J1.58, U5.12 (1A10)
A21_3V3: U5.44 (1B10); also elsewhere on the board
A22: J1.57, U5.13 (1A11)
A22_3V3: U5.43 (1B11); also elsewhere on the board
A23: J1.59, U5.14 (1A12)
A23_3V3: U5.42 (1B12); also elsewhere on the board
AS: J1.74, U6.12 (1B4)
AS_MB_3V3: U6.8 (1A4); also elsewhere on the board
BERR: J1.46, U5.23 (2A7)
BERR_3V3: U5.34 (2B7); also elsewhere on the board
BG: J1.64, U6.15 (2A3)
BGACK: J1.62, U6.13 (2A2)
BGACK_3V3: U6.7 (2B2); also elsewhere on the board
BG_3V3: U6.5 (2B3); also elsewhere on the board
BOSS: J1.20, U4.13 (1A11)
BOSS_3V3: U4.43 (1B11); also elsewhere on the board
BR: J1.60, U6.11 (2A1)
BR_3V3: U6.9 (2B1); also elsewhere on the board
C7M_3V3: R2.2; also elsewhere on the board
CCK: J1.16, U4.7 (1A6)
CCKQ: J1.14, U4.6 (1A5)
CCKQ_3V3: U4.50 (1B5), U17.6 (C)
CCK_3V3: U4.48 (1B6), U17.1 (B), U17.3 (A)
CDAC: J1.15, U4.9 (1A7)
CDAC_3V3: U4.47 (1B7); also elsewhere on the board
CFGIN: J1.12, J2.1
CFGIN_3V3: U4.51 (1B4); also elsewhere on the board
CFGOUT: J1.11, U4.4 (1A3)
CFGOUT_3V3: U4.52 (1B3); also elsewhere on the board
CLK7M: J1.7, U4.2 (1A1)
CLK7M_3V3: U4.54 (1B1); also elsewhere on the board
CP_INT6: U4.3 (1A2); also elsewhere on the board
CP_INT6_3V3: U4.53 (1B2); also elsewhere on the board
D0: J1.75, U7.41 (1A5)
D0_3V3: U7.8 (1B5); also elsewhere on the board
D1: J1.77, U7.43 (1A4)
D1_3V3: U7.6 (1B4); also elsewhere on the board
D2: J1.79, U7.44 (1A3)
D2_3V3: U7.5 (1B3); also elsewhere on the board
D3: J1.81, U7.46 (1A2)
D3_3V3: U7.3 (1B2); also elsewhere on the board
D4: J1.83, U7.47 (1A1)
D4_3V3: U7.2 (1B1); also elsewhere on the board
D5: J1.86, U7.40 (1A6)
D5_3V3: U7.9 (1B6); also elsewhere on the board
D6: J1.84, U7.38 (1A7)
D6_3V3: U7.11 (1B7); also elsewhere on the board
D7: J1.82, U7.37 (1A8)
D7_3V3: U7.12 (1B8); also elsewhere on the board
D8: J1.80, U7.36 (2A1)
D8_3V3: U7.13 (2B1); also elsewhere on the board
D9: J1.78, U7.35 (2A2)
D9_3V3: U7.14 (2B2); also elsewhere on the board
D10: J1.76, U7.33 (2A3)
D10_3V3: U7.16 (2B3); also elsewhere on the board
D11: J1.71, U7.32 (2A4)
D11_3V3: U7.17 (2B4); also elsewhere on the board
D12: J1.69, U7.26 (2A8)
D12_3V3: U7.23 (2B8); also elsewhere on the board
D13: J1.67, U7.27 (2A7)
D13_3V3: U7.22 (2B7); also elsewhere on the board
D14: J1.65, U7.29 (2A6)
D14_3V3: U7.20 (2B6); also elsewhere on the board
D15: J1.63, U7.30 (2A5)
D15_3V3: U7.19 (2B5); also elsewhere on the board
DATA_DIR: U7.1 (1DIR), U7.24 (2DIR); also elsewhere on the board
DTACK: J1.66, U6.17 (2A4)
DTACK_MB_3V3: U6.3 (2B4); also elsewhere on the board
E: J1.50, U5.25 (2A9)
E_3V3: U5.32 (2B9); also elsewhere on the board
FC0: J1.31, U5.18 (2A3)
FC0_3V3: U5.39 (2B3); also elsewhere on the board
FC1: J1.33, U5.16 (2A2)
FC1_3V3: U5.40 (2B2); also elsewhere on the board
FC2: J1.35, U5.15 (2A1)
FC2_3V3: U5.41 (2B1); also elsewhere on the board
GND: C1.2, C2.2, C3.1, C4.1, C5.1, C6.1, C7.1, C8.1, C12.1, C13.1, C14.1, C15.2, C16.1, C17.1, C18.1, C19.1, C20.1, C21.1, C22.1, C23.1, C24.1, C25.1, C26.1, C27.1, C28.1, C29.1, C30.1, C31.1, C32.1, C33.1, C34.1, C35.1, C36.1, C37.1, C38.1, C39.1, C40.1, C41.1, C42.1, C43.1, C47.1, C48.1, C51.1, C52.1, C53.1, C54.1, C55.1, C56.1, C57.1, C58.1, C59.1, C60.1, C61.1, C62.1, C63.1, C64.1, C65.1, C66.1, C67.1, C68.1, C69.1, C70.1, C71.1, C72.1, J1.1, J1.2, J1.3, J1.4, J1.13, J1.25, J1.37, J1.49, J1.61, J1.73, J1.85, J7.1, U1.1 (GND), U2.2 (GND), U3.2 (GND), U4.8 (GND), U4.15 (2A1), U4.19 (GND), U4.38 (GND), U4.49 (GND), U4.56 (1~OE), U5.8 (GND), U5.19 (GND), U5.38 (GND), U5.49 (GND), U5.55 (2~OE), U6.10 (GND), U6.19 (2~OE), U7.4 (GND_1), U7.10 (GND_2), U7.15 (GND_3), U7.21 (GND_4), U7.28 (GND_5), U7.34 (GND_6), U7.39 (GND_7), U7.45 (GND_8), U17.2 (GND); also elsewhere on the board
HLT: J1.55, U5.28 (2A12)
HLT_3V3: U5.29 (2B12); also elsewhere on the board
INT2: J1.19, U4.12 (1A10)
INT2_3V3: U4.44 (1B10); also elsewhere on the board
INT6: J1.22, U4.14 (1A12)
INT6_3V3: U4.42 (1B12); also elsewhere on the board
IPL0: J1.40, U5.20 (2A4)
IPL0_3V3: U5.37 (2B4); also elsewhere on the board
IPL1: J1.42, U5.21 (2A5)
IPL1_3V3: U5.36 (2B5); also elsewhere on the board
IPL2: J1.44, U5.22 (2A6)
IPL2_3V3: U5.35 (2B6); also elsewhere on the board
LDS: J1.70, U6.16 (1B2)
LDS_3V3: U6.4 (1A2); also elsewhere on the board
unnamed: J2.2, R21.2, U4.5 (1A4)
unnamed: R2.1, U17.4 (Y)
OE_ABUS: U4.55 (2~OE), U5.56 (1~OE), U6.1 (1~OE); also elsewhere on the board
OE_D_HIGH: U7.25 (2~OE); also elsewhere on the board
OE_D_LOW: U7.48 (1~OE); also elsewhere on the board
OVR: J1.17, U4.10 (1A8)
OVR_3V3: U4.46 (1B8); also elsewhere on the board
RST: J1.53, U5.27 (2A11); also elsewhere on the board
RST_3V3: U5.30 (2B11); also elsewhere on the board
RW: J1.68, U6.18 (1B1)
RW_3V3: U6.2 (1A1); also elsewhere on the board
UDS: J1.72, U6.14 (1B3)
UDS_3V3: U6.6 (1A3); also elsewhere on the board
VMA: J1.51, U5.26 (2A10)
VMA_3V3: U5.31 (2B10); also elsewhere on the board
VPA: J1.48, U5.24 (2A8)
VPA_3V3: U5.33 (2B8); also elsewhere on the board
XRDY: J1.18, U4.11 (1A9)
XRDY_3V3: U4.45 (1B9); also elsewhere on the board

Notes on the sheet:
CLK28M
-5V/-12V
+12V
0805 0.1uF = 100nF
3V3
4V3
Supply to FPGA I/O LVTTL
Supply to FET level shifters
Supply to ESP32-C5
0603 0.1uF = 100nF
1206 10uF
0402 0.1uF = 100nF
0603 0.01uF = 10nF

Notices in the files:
README.md:
This work is licensed under a
[Creative Commons Attribution-ShareAlike 4.0 International License][cc-by-sa].
